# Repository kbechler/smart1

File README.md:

# SmartHome - rozwiązania typu DIY

To repozytorium zawiera kilka pomysłow na rozwiąnia DIY integrujące się z Home Assistantem, Suplą i podobnymi systemami. Być może istnieją gotowce do kupienia na zagranicznych portalach aukcyjnych za niewielkie pieniądze, jednak satysfakcji ze zrobienia czegoś samodzielnie nie da się wycenić ;-)

## Co do czego?

* eagle/ - schematy i projekty płytek zrobione w Autodesk Eagle
* esphome/ - przykładowe konfiguracje dla ESPHome wykorzystujące daną płytkę

### LD-100
Prosty sterownik LEDów RGB (są tu tylko trzy kanały, więc sterować paskiem RGBW alob RGBWW się nie da) oraz WS2818 (paski LED, gdzie da się sterować każdą diodą oddzielnie). Oparty na ESP8266. Działa po WiFi z ESPHome (banalna integracja z Home Assistantem). UWAGA: Ten sterownik jest zasilany wyłącznie na 5V, więc większość popularnych taśm LED (wymagających 12V) nie będzie z nim działać.
[TODO: Zrobić próby i określić prądy, które AO3400 wytrzymują bez chłodzenia] 

### UD-100
Prosty sterownik LEDów RGBW (cztery kanały) oparty na ESP8266 oraz tranzystorach IRLR024N. Dodatkowo, zamiast czwartego kanału na płytce znalazło się miejsce dla czujnika temperatury (DS18B20) lub podczerwieni (TSOP1736). Nominalnie zasilany z 12V, więc kompatyilny z większością popularnych tasiemek LED (mono, RGB, RGBW).

## Jak to zaprogramować?

### ESP8266, ESP32
Projekty oparte na ESP8266 i ESP32 wymagają do programowania konwertera USB-RS232. Koniecznie ustawionego na 3.3V (5V może usmażyć nasze ESP) oraz programu esptool (https://github.com/espressif/esptool). Wszystkie płytki (jeżeli w opisie nie zaznaczyłem inaczej) posiadają złącze do programowania w formacie (GND-RX-TX-RST-VCC).

W najprostszej wersji używamy tylko pierwszych trzech PINów oraz "natywnego" zasilania płytki (podczas programowania chip ESP potrzebuje sporo prądu i duża część konwerterów USB-RS232 nie daje sobie z tym rady).

W wielkim skrócie i w najprostszym przypadku podłączamy trzy pierwsze PINy (czyli GND, RX, TX), naciskamy switch podpięty do portu GPIO0, podpinamy zasilanie i ruchamiamy "esphome run jakis_plik.yaml".

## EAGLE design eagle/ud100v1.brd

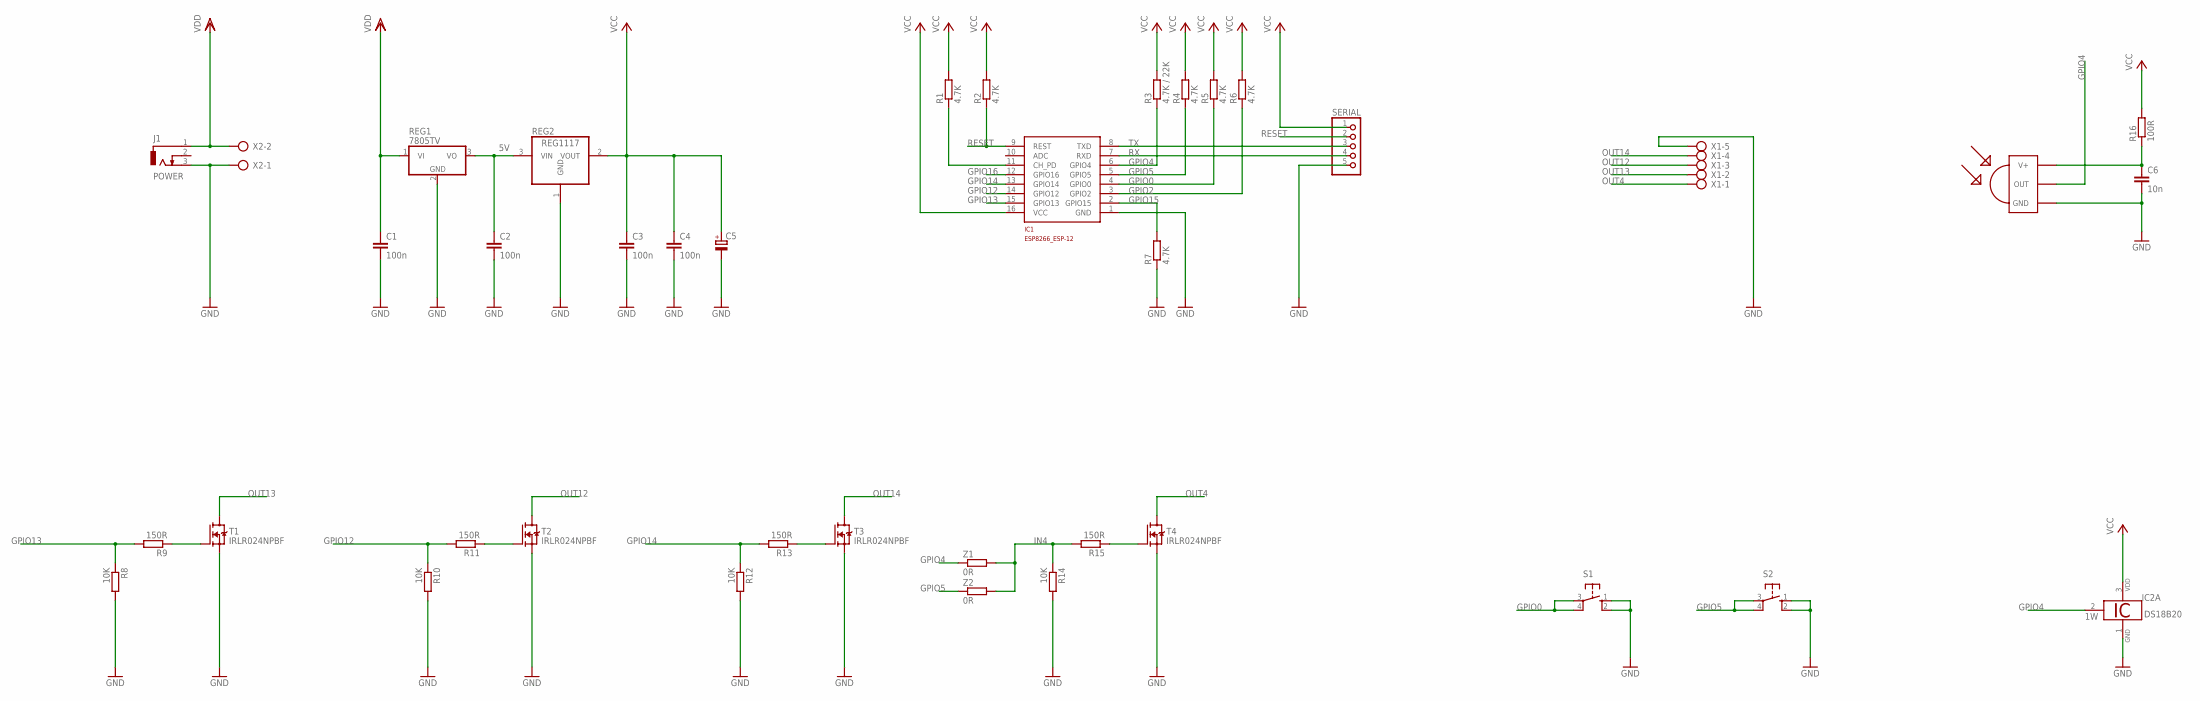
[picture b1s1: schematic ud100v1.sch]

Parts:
C1, C2, C3, C4: 100n; C1206
C5: CPOL-EUUD-6,3X8,8; UD-6,3X5,8_NICHICON
C6: 10n; C1206
IC1: ESP8266_ESP-12; ESP8266-ESP12
IC2: DS18B20; TO92-
J1: POWER; DCJ0303
R1, R2, R4, R5, R6, R7: 4.7K; R1206
R3: 4.7K / 22K; R1206
R8, R10, R12, R14: 10K; R1206
R9, R11, R13, R15: 150R; R1206
R16: 100R; R1206
REG1: 7805TV; TO220V
REG2: REG1117; SOT223
S1, S2: 10-XX; B3F-10XX
SERIAL: PINHD-1X5; 1X05
T1, T2, T3, T4: IRLR024NPBF; DPAK_TO252
U$1: TSOP1736; TSOP17XX
X1: AK500/5
X2: AK500/2
Z1, Z2: 0R; R0805

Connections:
5V: C2.1, REG1.3 (VO), REG2.3 (VIN)
GND: C1.2, C2.2, C3.2, C4.2, C5.-, C6.2, IC1.1 (GND), IC2.1 (GND), J1.3, R7.1, R8.2, R10.2, R12.2, R14.2, REG1.2 (GND), REG2.1 (GND), S1.1 (S), S1.2 (S1), S2.1 (S), S2.2 (S1), SERIAL.5, T1.3 (S), T2.3 (S), T3.3 (S), T4.3 (S), U$1.GND, X1.5, X2.1
GPIO0: IC1.4 (GPIO0), R5.1, S1.3, S1.4 (P1)
GPIO2: IC1.3 (GPIO2), R6.1
GPIO4: IC1.6 (GPIO4), IC2.2 (1W), R3.1, U$1.OUT, Z1.1
GPIO5: IC1.5 (GPIO5), R4.1, S2.3, S2.4 (P1), Z2.1
GPIO12: IC1.14 (GPIO12), R10.1, R11.2
GPIO13: IC1.15 (GPIO13), R8.1, R9.2
GPIO14: IC1.13 (GPIO14), R12.1, R13.2
GPIO15: IC1.2 (GPIO15), R7.2
GPIO16: IC1.12 (GPIO16)
IN4: R14.1, R15.2, Z1.2, Z2.2
unnamed: R15.1, T4.1 (G)
unnamed: IC1.11 (CH_PD), R1.1
unnamed: C6.1, R16.1, U$1.V+
unnamed: R13.1, T3.1 (G)
unnamed: R9.1, T1.1 (G)
unnamed: R11.1, T2.1 (G)
OUT4: T4.2 (D), X1.1
OUT12: T2.2 (D), X1.3
OUT13: T1.2 (D), X1.2
OUT14: T3.2 (D), X1.4
RESET: IC1.9 (REST), R2.1, SERIAL.2
RX: IC1.7 (RXD), SERIAL.4
TX: IC1.8 (TXD), SERIAL.3
VCC: C3.1, C4.1, C5.+, IC1.16 (VCC), IC2.3 (VDD), R1.2, R2.2, R3.2, R4.2, R5.2, R6.2, R16.2, REG2.2 (VOUT), SERIAL.1
VDD: C1.1, J1.1, REG1.1 (VI), X2.2

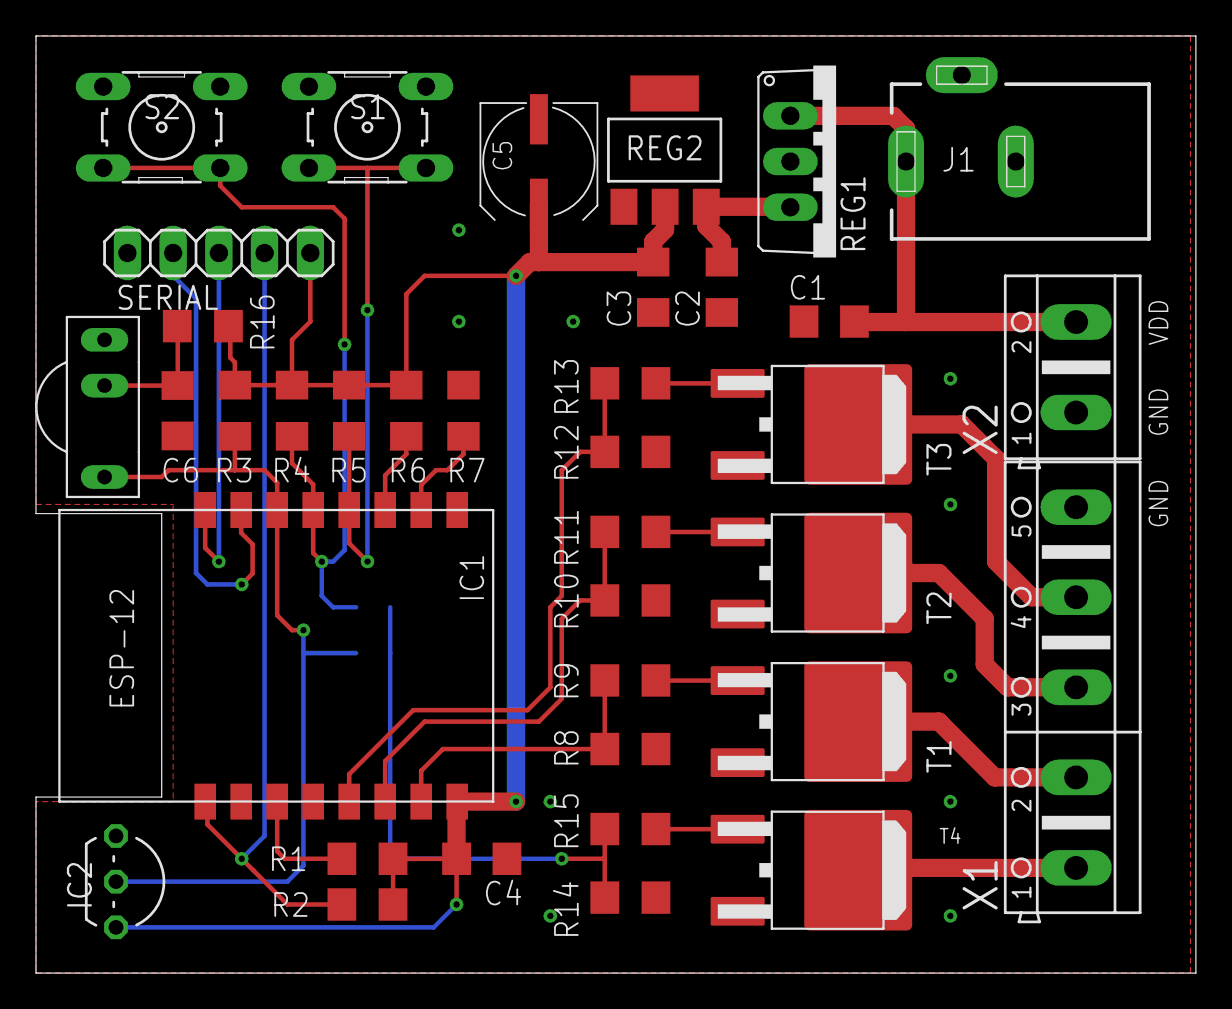
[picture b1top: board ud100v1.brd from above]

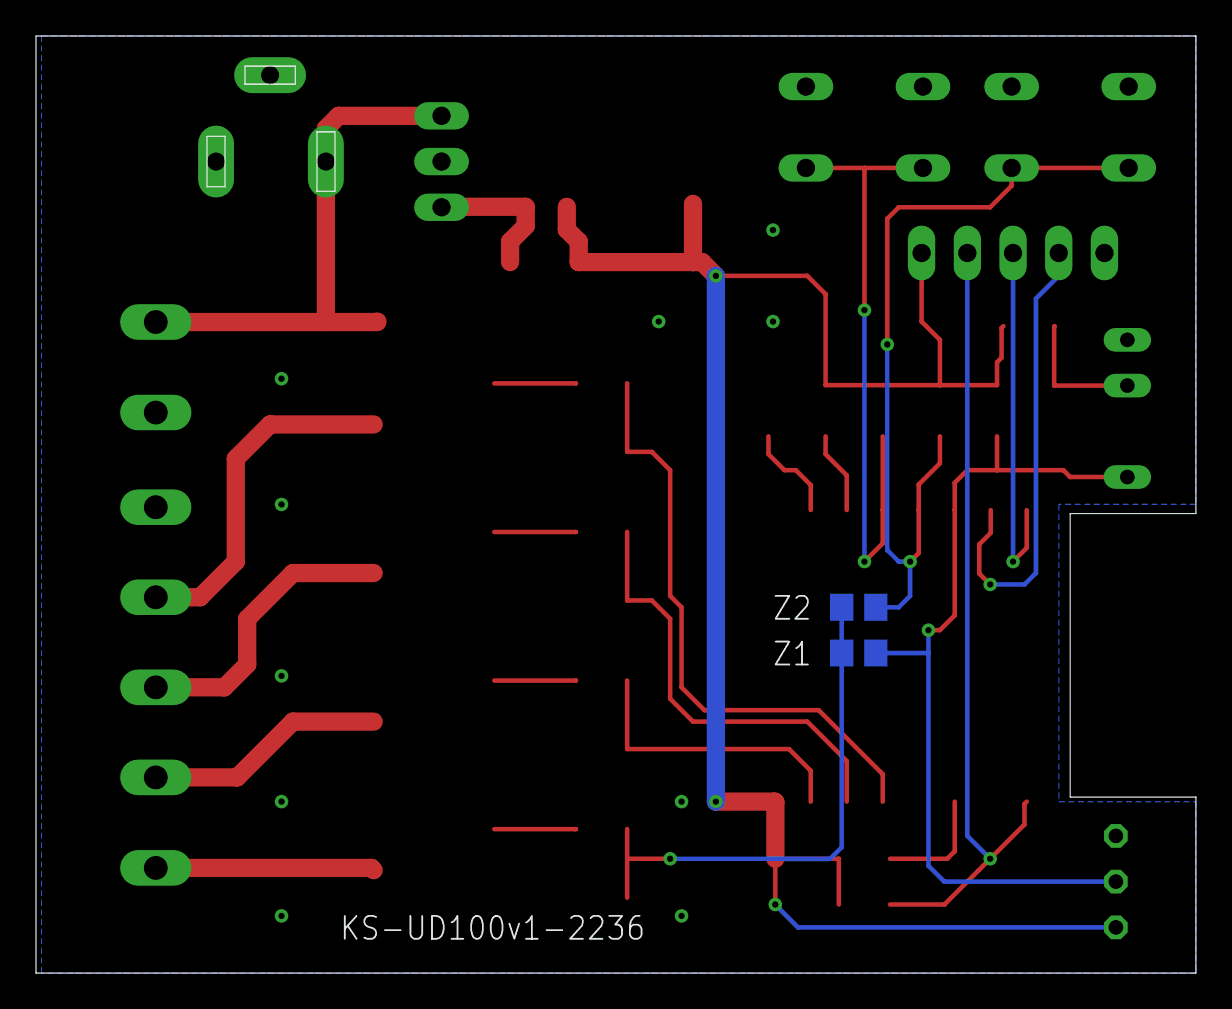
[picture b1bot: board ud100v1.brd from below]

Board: 2 copper layers, 64.4 x 52.1 mm, 39 parts (2 on the bottom side), 26 nets.

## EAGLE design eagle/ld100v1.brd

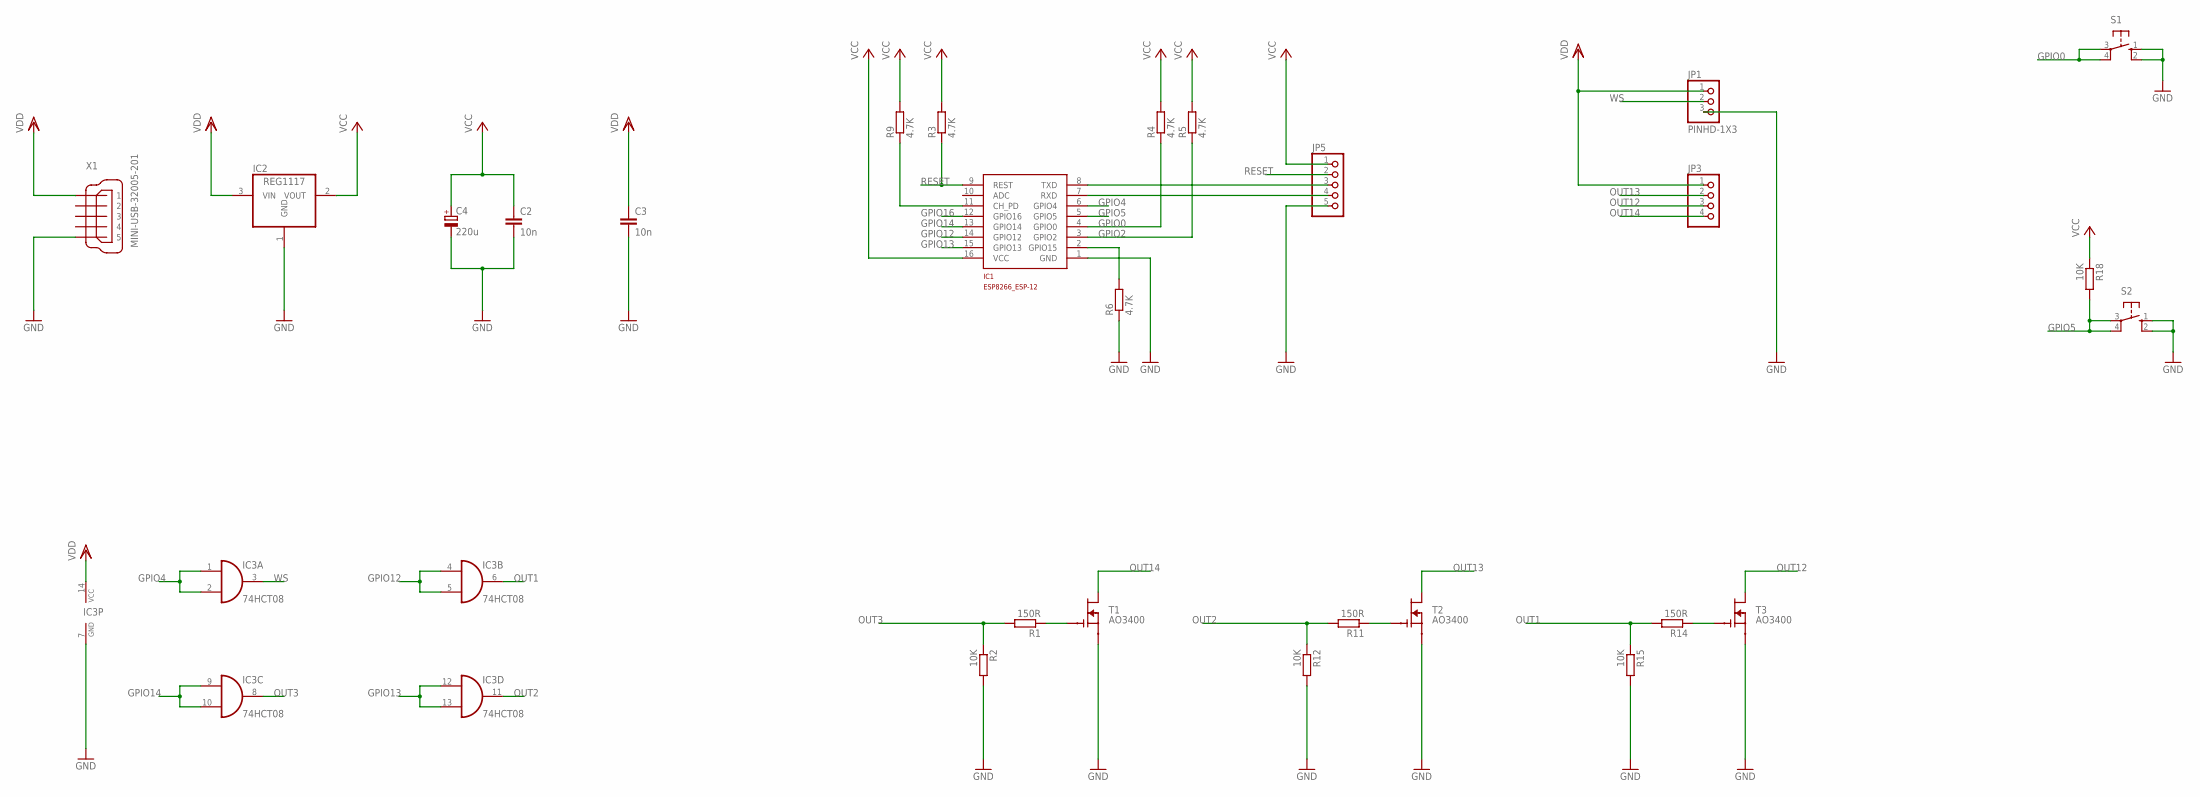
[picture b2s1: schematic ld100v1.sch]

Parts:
C2, C3: 10n; C1206
C4: 220u; UD-6,3X5,8_NICHICON
IC1: ESP8266_ESP-12; ESP8266-ESP12
IC2: REG1117; SOT223
IC3: 74HCT08; SO14
JP1: PINHD-1X3; 1X03
JP3: PINHD-1X4; 1X04
JP5: PINHD-1X5; 1X05
R1, R11, R14: 150R; R1206
R2, R12, R15, R18: 10K; R1206
R3, R4, R5, R6, R9: 4.7K; R1206
S1, S2: 10-XX; B3F-10XX
T1, T2, T3: AO3400; SOT23
X1: MINI-USB-32005-201; 32005-201

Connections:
GND: C2.2, C3.2, C4.-, IC1.1 (GND), IC2.1 (GND), IC3.7 (GND), JP1.3, JP5.5, R2.2, R6.1, R12.2, R15.2, S1.1 (S), S1.2 (S1), S2.1 (S), S2.2 (S1), T1.2 (S), T2.2 (S), T3.2 (S), X1.5
GPIO0: IC1.4 (GPIO0), R4.1, S1.3, S1.4 (P1)
GPIO2: IC1.3 (GPIO2), R5.1
GPIO4: IC1.6 (GPIO4), IC3.1 (I0), IC3.2 (I1)
GPIO5: IC1.5 (GPIO5), R18.2, S2.3, S2.4 (P1)
GPIO12: IC1.14 (GPIO12), IC3.4 (I0), IC3.5 (I1)
GPIO13: IC1.15 (GPIO13), IC3.12 (I0), IC3.13 (I1)
GPIO14: IC1.13 (GPIO14), IC3.9 (I0), IC3.10 (I1)
GPIO16: IC1.12 (GPIO16)
unnamed: IC1.8 (TXD), JP5.3
unnamed: IC1.7 (RXD), JP5.4
unnamed: IC1.11 (CH_PD), R9.1
unnamed: IC1.2 (GPIO15), R6.2
unnamed: R1.1, T1.1 (G)
unnamed: R11.1, T2.1 (G)
unnamed: R14.1, T3.1 (G)
OUT1: IC3.6 (O), R14.2, R15.1
OUT2: IC3.11 (O), R11.2, R12.1
OUT3: IC3.8 (O), R1.2, R2.1
OUT12: JP3.3, T3.3 (D)
OUT13: JP3.2, T2.3 (D)
OUT14: JP3.4, T1.3 (D)
RESET: IC1.9 (REST), JP5.2, R3.1
VCC: C2.1, C4.+, IC1.16 (VCC), IC2.2 (VOUT), JP5.1, R3.2, R4.2, R5.2, R9.2, R18.1
VDD: C3.1, IC2.3 (VIN), IC3.14 (VCC), JP1.1, JP3.1, X1.1
WS: IC3.3 (O), JP1.2

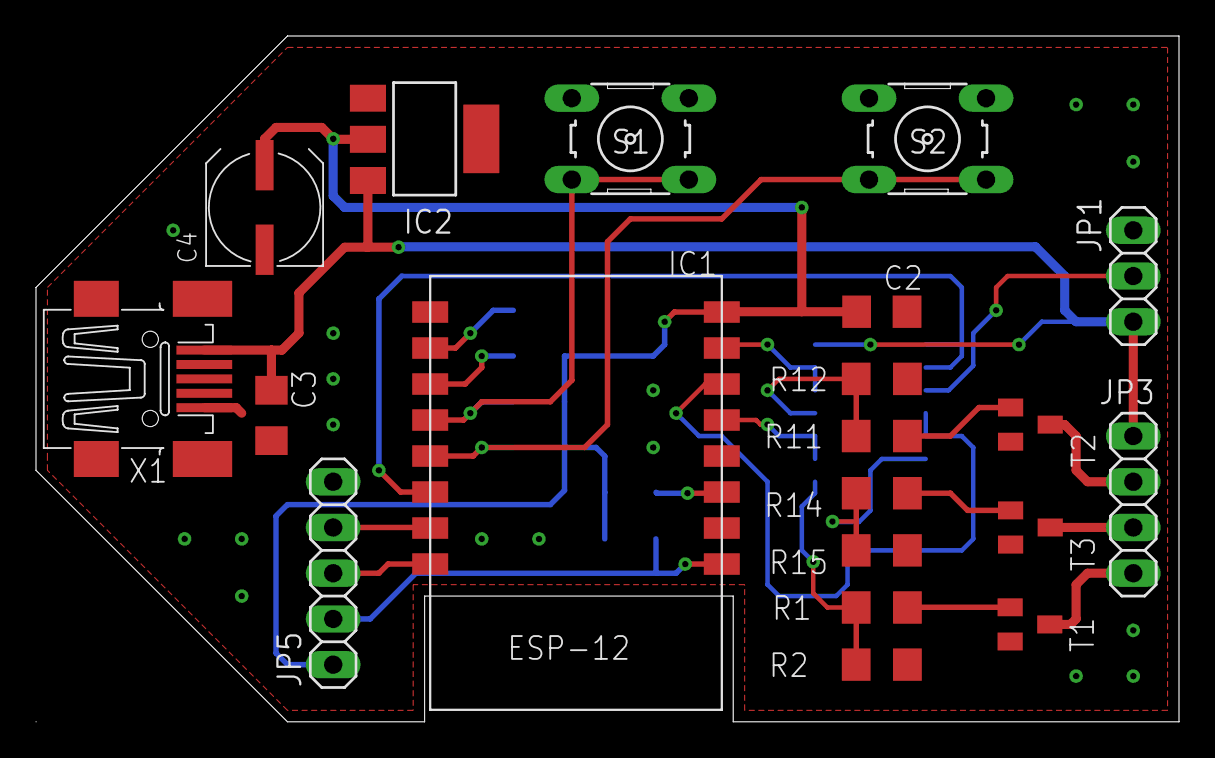
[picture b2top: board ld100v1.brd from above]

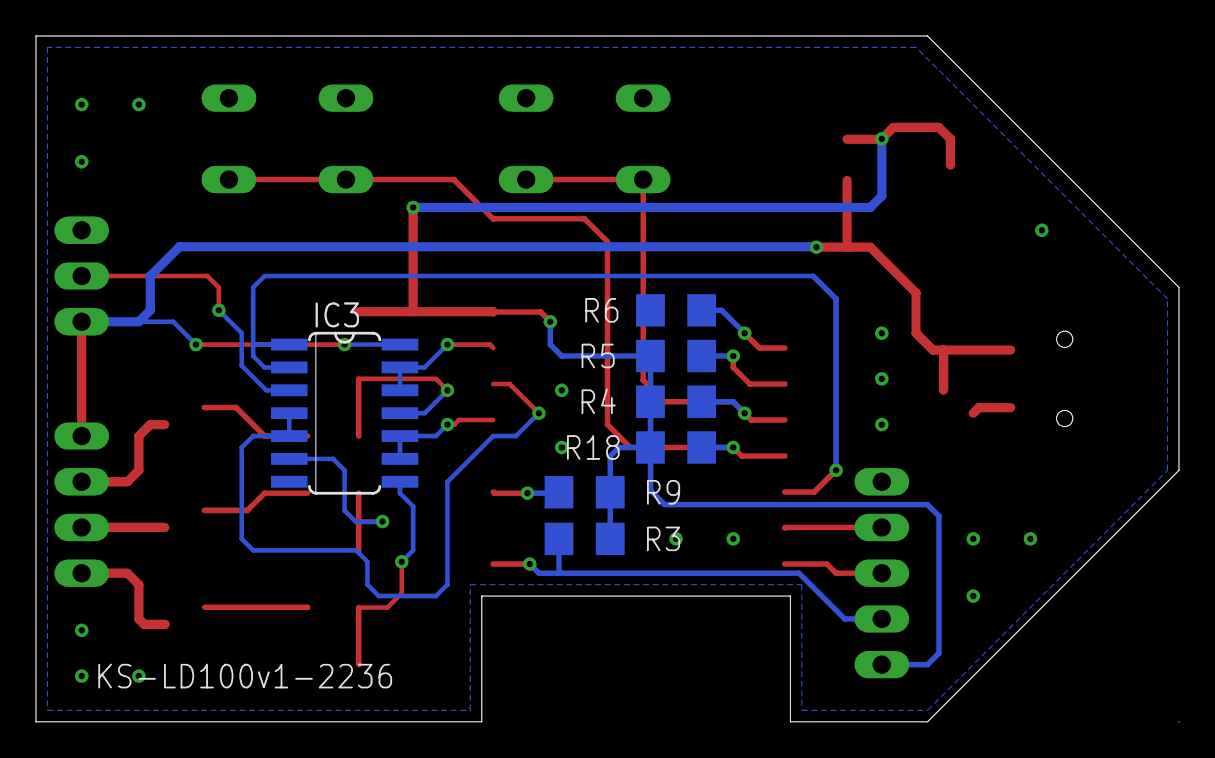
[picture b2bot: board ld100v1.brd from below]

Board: 2 copper layers, 63.5 x 38.1 mm, 27 parts (7 on the bottom side), 25 nets.

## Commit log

2022-11-27 init
2022-11-28 ld100, ud100
2022-11-28 images for ld100, ud100
2022-11-28 first readme
